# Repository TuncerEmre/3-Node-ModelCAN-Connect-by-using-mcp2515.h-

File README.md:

CAN Bus Communication Project

This project demonstrates CAN bus communication between multiple nodes using the MCP2515 module. The system is implemented with the Arduino IDE and C++.

Overview
The project consists of three main nodes:

Arduino Nano Remote Control Node

Receives data from an RF wireless control module.
Sends control data to the Atmega 1 Engine Control Node.
Atmega 1 Engine Control Node

Manages the motor driver (L298N).
Controls a display screen to show data from sensors.

Atmega 2 Sensors Node

Processes data from various sensors, including:

RPM Sensor (LM393)

Distance Sensor (HC-SR04)

Components Used

CAN Module: MCP2515

Libraries Used: MCP2515

Development Environment: Arduino IDE

Programming Language: C++

Installation

Clone the Repository:

git clone https://github.com/TuncerEmre/3-Node-ModelCAN-Connect-by-using-mcp2515.h-.git

Install Required Libraries:

Install the MCP2515 library from the Arduino Library Manager or by downloading it from GitHub.

Upload the Code:

-Open the Arduino IDE.

-Load the respective sketch for each node.

-Connect each microcontroller to your computer and upload the code.

Usage

Remote Control Node:

Use the RF wireless control module to send commands.

The node will transmit data to the Atmega 1 Engine Control Node via CAN bus.

Engine Control Node:

The node will drive the motor through the L298N driver.

It will also display sensor data on the screen.

Sensors Node:

Collects and processes data from the RPM sensor and distance sensor.

Sends processed data to the Engine Control Node to show the data on LCD screen.

All circuits are soldered on perforated pertinax. 

Note: The final car is intended as a demonstration for the purposes of this project, which serves as the final assignment for a course. Therefore, the project is subject to a strict deadline. Additional implementations and upgrades may occur in the future.

some photos of demo car:

Contributing

Feel free to contribute to this project by submitting pull requests or issues. For detailed contribution guidelines, please refer to CONTRIBUTING.md.

License
This project is licensed under the MIT License. See the LICENSE file for details.

Contact
For any questions or comments, please contact Emre Tuncer.

E-mail: emretuncer396@gmail.com

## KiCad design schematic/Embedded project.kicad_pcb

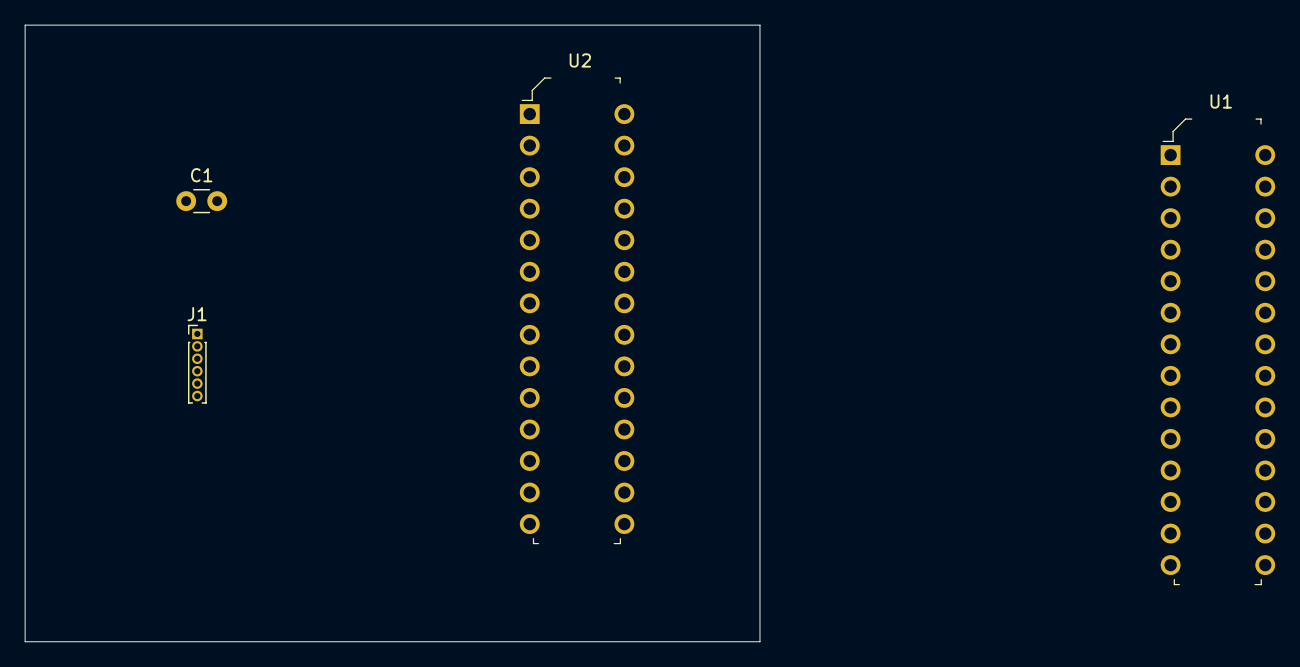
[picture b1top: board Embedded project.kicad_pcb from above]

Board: 2 copper layers, 59.2 x 49.7 mm, 4 parts (0 on the bottom side), 5 nets, no tracks yet.

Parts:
C1: 100nf; C_Disc_D3.0mm_W1.6mm_P2.50mm
J1: Conn_01x06; PinHeader_1x06_P1.00mm_Vertical
U1, U2: ATMEGA328P-PU; DIP-28_W7.62mm

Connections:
/Cod upload diagram/DTR: C1.1, C1.2, J1.6, U2.1 (PC6)
/Cod upload diagram/GND: J1.1, U2.8 (GND)
/Cod upload diagram/RX: J1.4, U2.2 (PD0)
/Cod upload diagram/TX: J1.5, U2.3 (PD1)
/Cod upload diagram/VCC: J1.3, U2.7 (VCC)

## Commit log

2024-07-21 Added all necessary files
2024-07-21 create a Readme.md file
2024-07-25 Update README.md
    ADDED some photos to README.mf
2024-07-25 Update README.md
    Additional photos added
2024-07-25 Photes folder have created. Some photos added.
2024-07-25 Delete Readme.md
    Wrong readme file deleted
2024-07-25 Wrong readme.md file deleted
